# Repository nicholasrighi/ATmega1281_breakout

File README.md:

# ATmega1281_breakout
Breakout board for the ATmega1281 to allow for faster development using the ATmega1281/2561 microcontrollers

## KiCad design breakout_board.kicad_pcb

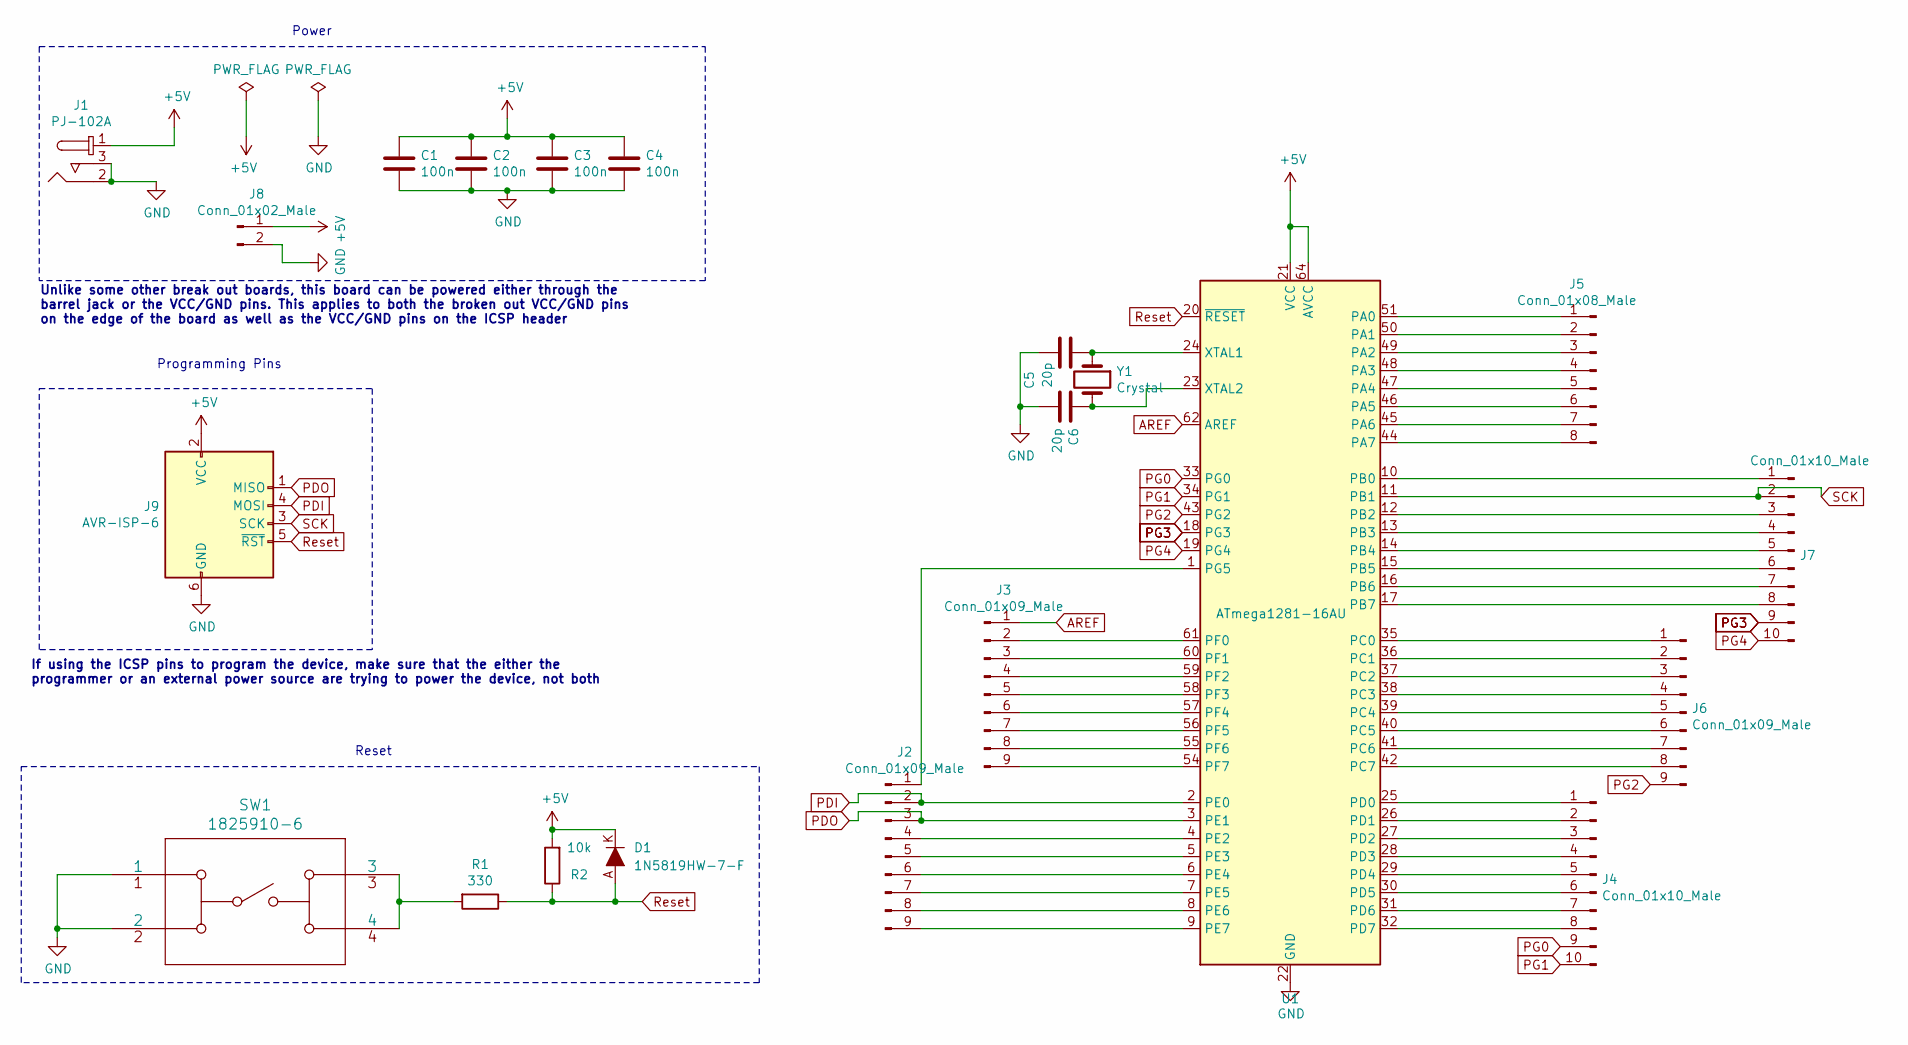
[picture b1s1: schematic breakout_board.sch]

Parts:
C1, C2, C3, C4: 100n; C_0805_2012Metric_Pad1.15x1.40mm_HandSolder
C5, C6: 20p; C_0805_2012Metric_Pad1.15x1.40mm_HandSolder
D1: 1N5819HW-7-F; SOD-123; MPN 1N5819HW-7-F; Digi-Key_PN 1N5819HW-FDICT-ND
J1: PJ-102A; Barrel_Jack_5.5mmODx2.1mmID_PJ-102A; MPN PJ-102A; Digi-Key_PN CP-102A-ND
J2, J3, J6: Conn_01x09_Male; PinSocket_1x09_P2.54mm_Vertical
J4, J7: Conn_01x10_Male; PinSocket_1x10_P2.54mm_Vertical
J5: Conn_01x08_Male; PinSocket_1x08_P2.54mm_Vertical
J8: Conn_01x02_Male; PinSocket_1x02_P2.54mm_Vertical
J9: AVR-ISP-6; PinHeader_2x03_P2.54mm_Vertical
R1: 330; R_0805_2012Metric_Pad1.15x1.40mm_HandSolder
R2: 10k; R_0805_2012Metric_Pad1.15x1.40mm_HandSolder
SW1: 1825910-6
U1: ATmega1281-16AU; TQFP-64_14x14mm_P0.8mm
Y1: Crystal; Crystal_HC49-U_Vertical

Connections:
+5V: C1.1, C2.1, C3.1, C4.1, D1.K, J1.1, J8.1, J9.2 (VCC), R2.2, U1.21 (VCC), U1.52 (VCC), U1.64 (AVCC)
AREF: J3.1, U1.62 (AREF)
GND: C1.2, C2.2, C3.2, C4.2, C5.2, C6.2, J1.2, J1.3, J8.2, J9.6 (GND), SW1.1, SW1.2, U1.22 (GND), U1.53 (GND), U1.63 (GND)
unnamed: C5.1, U1.24 (XTAL1), Y1.1
unnamed: C6.1, U1.23 (XTAL2), Y1.2
unnamed: J2.1, U1.1 (PG5)
unnamed: J2.4, U1.4 (PE2)
unnamed: J2.5, U1.5 (PE3)
unnamed: J2.6, U1.6 (PE4)
unnamed: J2.7, U1.7 (PE5)
unnamed: J2.8, U1.8 (PE6)
unnamed: J2.9, U1.9 (PE7)
unnamed: J3.2, U1.61 (PF0)
unnamed: J3.3, U1.60 (PF1)
unnamed: J3.4, U1.59 (PF2)
unnamed: J3.5, U1.58 (PF3)
unnamed: J3.6, U1.57 (PF4)
unnamed: J3.7, U1.56 (PF5)
unnamed: J3.8, U1.55 (PF6)
unnamed: J3.9, U1.54 (PF7)
unnamed: J4.1, U1.25 (PD0)
unnamed: J4.2, U1.26 (PD1)
unnamed: J4.3, U1.27 (PD2)
unnamed: J4.4, U1.28 (PD3)
unnamed: J4.5, U1.29 (PD4)
unnamed: J4.6, U1.30 (PD5)
unnamed: J4.7, U1.31 (PD6)
unnamed: J4.8, U1.32 (PD7)
unnamed: J5.1, U1.51 (PA0)
unnamed: J5.2, U1.50 (PA1)
unnamed: J5.3, U1.49 (PA2)
unnamed: J5.4, U1.48 (PA3)
unnamed: J5.5, U1.47 (PA4)
unnamed: J5.6, U1.46 (PA5)
unnamed: J5.7, U1.45 (PA6)
unnamed: J5.8, U1.44 (PA7)
unnamed: J6.1, U1.35 (PC0)
unnamed: J6.2, U1.36 (PC1)
unnamed: J6.3, U1.37 (PC2)
unnamed: J6.4, U1.38 (PC3)
unnamed: J6.5, U1.39 (PC4)
unnamed: J6.6, U1.40 (PC5)
unnamed: J6.7, U1.41 (PC6)
unnamed: J6.8, U1.42 (PC7)
unnamed: J7.1, U1.10 (PB0)
unnamed: J7.3, U1.12 (PB2)
unnamed: J7.4, U1.13 (PB3)
unnamed: J7.5, U1.14 (PB4)
unnamed: J7.6, U1.15 (PB5)
unnamed: J7.7, U1.16 (PB6)
unnamed: J7.8, U1.17 (PB7)
unnamed: R1.2, SW1.3, SW1.4
PDI: J2.2, J9.4 (MOSI), U1.2 (PE0)
PDO: J2.3, J9.1 (MISO), U1.3 (PE1)
PG0: J4.9, U1.33 (PG0)
PG1: J4.10, U1.34 (PG1)
PG2: J6.9, U1.43 (PG2)
PG3: J7.9, U1.18 (PG3)
PG4: J7.10, U1.19 (PG4)
Reset: D1.A, J9.5 (~RST), R1.1, R2.1, U1.20 (~RESET)
SCK: J7.2, J9.3 (SCK), U1.11 (PB1)

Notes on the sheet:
Programming Pins
Power
Unlike some other break out boards, this board can be powered either through the barrel jack or the VCC/GND pins. This applies to both the broken out VCC/GND pins on the edge of the board as well as the VCC/GND pins on the ICSP header
If using the ICSP pins to program the device, make sure that the either the programmer or an external power source are trying to power the device, not both
Reset

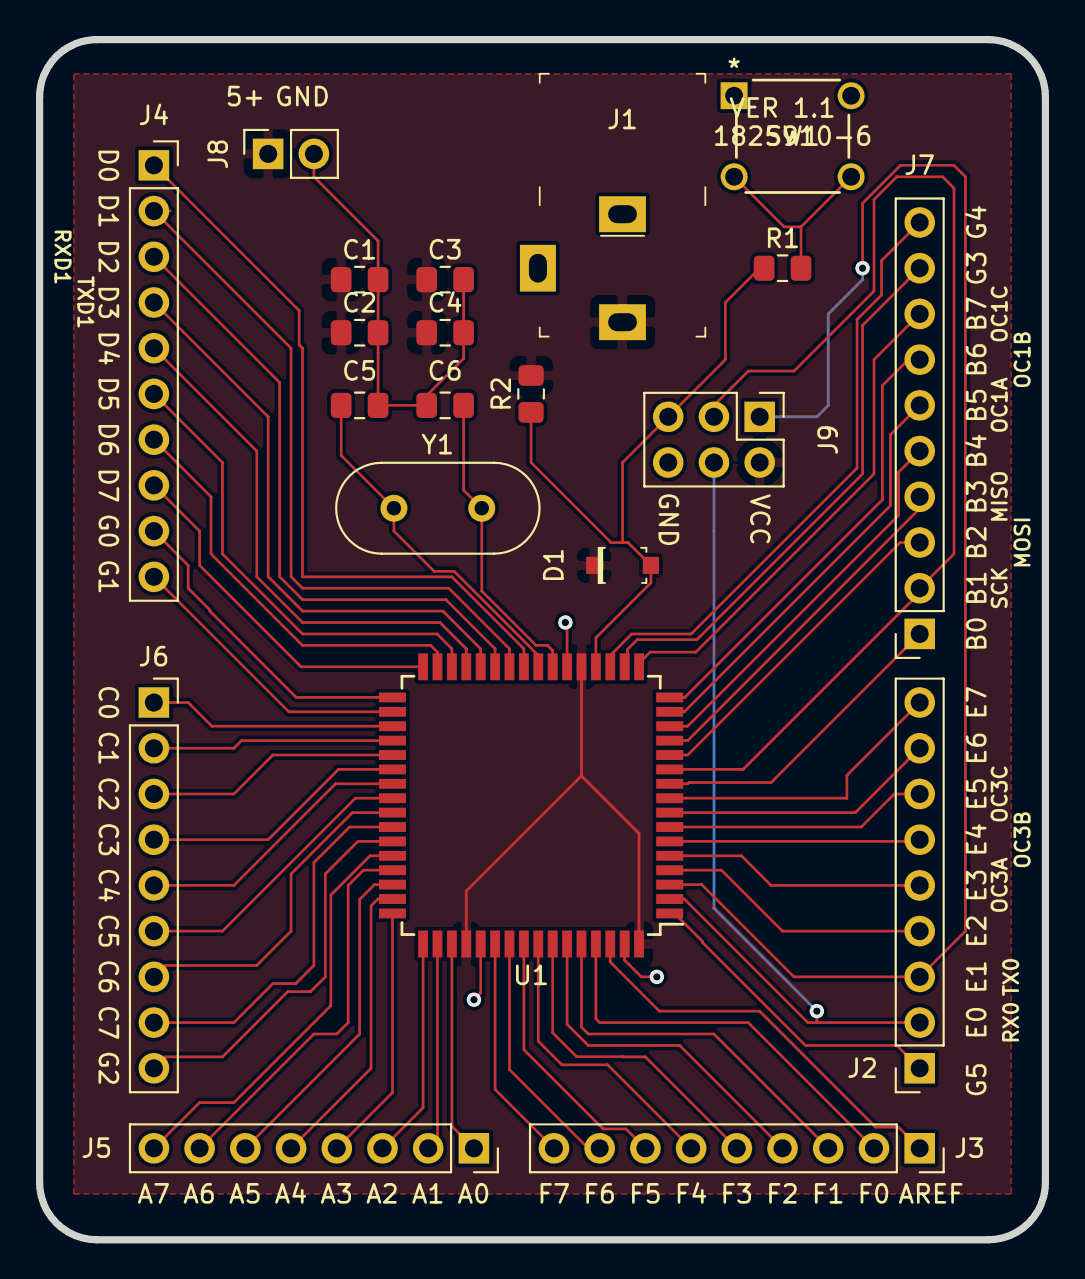
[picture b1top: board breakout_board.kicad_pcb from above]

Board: 2 copper layers, 55.9 x 66.7 mm, 21 parts (0 on the bottom side), 61 nets.

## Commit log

2020-07-23 Add files via upload
    Changed ISP pin header to align with USBasp pinout. Swapped from ATmega2561 to ATmega1281 to allow for the manufacturer to solder the components on themselves (only diff. between 2561 and 1281 is the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
2020-08-10 Add files via upload
    Fixed incorrect silkscreen pin labels, added silkscreen labels for pin functionality. Added reset button to reset the microcontroller

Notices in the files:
parts and their libraries:
Copyright 2016 Accelerated Designs. All rights reserved.
